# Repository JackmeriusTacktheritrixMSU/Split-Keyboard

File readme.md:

This is a split keyboard loosely based on Hack Club's (https://stasis.hackclub.com/starter-projects/split-keyboard.)
It runs from bluetooth, on two NRF52840 Pro Micro clone boards that you can get on aliexpress for cheap. 

Why'd I make it?
Its a bit of a deviation from the standard split keyboard dealy. Generally people use these same switches, but they

A. Expose the MCU on the top face of the keyboard halves
B. Use very few keys (Like a 45 percent keyboard or something along those lines)
and 
C. Use super flat, spread out keycaps.
I'm not crazy about any of these. I like traditional keyboards okay, and I have no idea how people remember which key is which on their splits. I wanted mine to be more standard- with the split for ergnomics but fairly status quo
everywhere else. I like the feeling of regular keycaps-- I like the look as well. I wanted to design my own keycaps. I got the little plug insert bits just from user fivedee on printables \
(https://www.printables.com/model/1069263-15x15-minimal-spaced-kailh-choc-keycap/files)  
Everything else I cut out and built my own. The result is some monster sized caps- turning low profile switches into a very much not low profile keyboard- which is what I wanted, but I might need to change things in the future and 
make my caps lighter. As of now they are untested. 

The design is screws coming up from the bottom. The two sides mesh together with a nice offset surface.

The PCB is actually reversed for the final- because it has kailh hot swap switches on it

BOM
| Item | Count | Price Per Unit | Total Price | Link | Status |
|---|---:|---:|---:|---|---|
| M2 Heatset Inserts (3.2 x 3.2mm) | 21 | N/A | N/A | N/A | Have |
| NRF52840 Dev Board | Pack x2 | N/A | $0.99 | [Link](https://www.aliexpress.us/item/3256807018711621.html?spm=a2g0o.cart.0.0.46a538daSh2DJS&mp=1&pdp_npi=6%40dis%21USD%21USD%207.23%21USD%200.99%21%21USD%200.99%21%21%21%402101e83017737027362077455e2f9f%2112000052145987931%21ct%21US%217434485779%21%211%210%21&_gl=1*qex46*_gcl_aw*R0NMLjE3NzM3MDE3OTIuQ2p3S0NBancxTjdOQmhBb0Vpd0FjUGNocDZjZm9MbWJFeHJpeEhseGhxQm5sM19CVXFTZWdTNlA5QUllUGg1SnFUQW82TlVySkJXMzF4b0N3UUVRQXZEX0J3RQ..*_gcl_dc*R0NMLjE3NzM3MDE3OTIuQ2p3S0NBancxTjdOQmhBb0Vpd0FjUGNocDZjZm9MbWJFeHJpeEhseGhxQm5sM19CVXFTZWdTNlA5QUllUGg1SnFUQW82TlVySkJXMzF4b0N3UUVRQXZEX0J3RQ..*_gcl_au*NDE0NzgwMTk1LjE3NzMxNzg3NzI.*_ga*MjEzOTYzMzUyMTA0MjEwOC4xNzczMTc4NzcxNDEx*_ga_VED1YSGNC7*czE3NzM3MDA1MzQkbzUkZzEkdDE3NzM3MDI3MzkkajMxJGwwJGgw&gatewayAdapt=glo2usa) | Need |
| PCB | Pack x5 (dev min) | N/A | $25.70 | N/A? | Need |
| Li-ion Poly Battery 5000mAh | Pack x2 | N/A | $14.13 | [Link](https://www.aliexpress.us/item/3256809787664995.html?spm=a2g0o.cart.0.0.610438daQ8KPR9&mp=1&pdp_npi=6%40dis%21USD%21USD%2031.41%21USD%2014.13%21%21USD%2014.13%21%21%21%402101e83017737024323317715e2f9f%2112000050732619666%21ct%21US%217434485779%21%211%210%21&_gl=1*4rofoi*_gcl_aw*R0NMLjE3NzM3MDE3OTIuQ2p3S0NBancxTjdOQmhBb0Vpd0FjUGNocDZjZm9MbWJFeHJpeEhseGhxQm5sM19CVXFTZWdTNlA5QUllUGg1SnFUQW82TlVySkJXMzF4b0N3UUVRQXZEX0J3RQ..*_gcl_dc*R0NMLjE3NzM3MDE3OTIuQ2p3S0NBancxTjdOQmhBb0Vpd0FjUGNocDZjZm9MbWJFeHJpeEhseGhxQm5sM19CVXFTZWdTNlA5QUllUGg1SnFUQW82TlVySkJXMzF4b0N3UUVRQXZEX0J3RQ..*_gcl_au*NDE0NzgwMTk1LjE3NzMxNzg3NzI.*_ga*MjEzOTYzMzUyMTA0MjEwOC4xNzczMTc4NzcxNDEx*_ga_VED1YSGNC7*czE3NzM3MDA1MzQkbzUkZzEkdDE3NzM3MDI3NDUkajI1JGwwJGgw&gatewayAdapt=glo2usa) | Need |
| Choc V1 Switches | 77 | N/A | N/A | [Link](https://www.aliexpress.us/item/3256809185516557.html?src=google&pdp_npi=4%40dis%21USD%217.09%217.09%21%21%21%21%21%40%2112000048898680192%21ppc%21%21%21&src=google&albch=shopping&acnt=708-803-3821&isdl=y&slnk=&plac=&mtctp=&albbt=Google_7_shopping&aff_platform=google&aff_short_key=UneMJZVf&gclsrc=aw.ds&albagn=888888&ds_e_adid=&ds_e_matchtype=&ds_e_device=c&ds_e_network=x&ds_e_product_group_id=&ds_e_product_id=en3256809185516557&ds_e_product_merchant_id=5337023700&ds_e_product_country=US&ds_e_product_language=en&ds_e_product_channel=online&ds_e_product_store_id=&ds_url_v=2&albcp=19558607238&albag=&isSmbAutoCall=false&needSmbHouyi=false&gad_source=1&gad_campaignid=19566915268&gbraid=0AAAAAD6I-hHE-H-7J2P63qEfKvxg4aSxQ&gclid=CjwKCAjw1N7NBhAoEiwAcPchp6cfoLmbExrixHlxhqBnl3_BUqSegS6P9AIePh5JqTAo6NUrJBW31xoCwQEQAvD_BwE&gatewayAdapt=glo2usa) | Have |
| PG1350 Sockets | 77 | N/A | N/A | [Link](https://www.aliexpress.us/item/3256805079542148.html?src=google&pdp_npi=4%40dis%21USD%211.54%211.11%21%21%21%21%21%40%2112000032415288517%21ppc%21%21%21&src=google&albch=shopping&acnt=708-803-3821&isdl=y&slnk=&plac=&mtctp=&albbt=Google_7_shopping&aff_platform=google&aff_short_key=UneMJZVf&gclsrc=aw.ds&albagn=888888&ds_e_adid=&ds_e_matchtype=&ds_e_device=c&ds_e_network=x&ds_e_product_group_id=&ds_e_product_id=en3256805079542148&ds_e_product_merchant_id=109258156&ds_e_product_country=US&ds_e_product_language=en&ds_e_product_channel=online&ds_e_product_store_id=&ds_url_v=2&albcp=19558607238&albag=&isSmbAutoCall=false&needSmbHouyi=false&gad_source=1&gad_campaignid=19566915268&gbraid=0AAAAAD6I-hHE-H-7J2P63qEfKvxg4aSxQ&gclid=CjwKCAjw1N7NBhAoEiwAcPchp13K3jXwFwk-rPK55fXNXv5V-aJNthOR1-a6wdnraypLKRLxYWzpIRoCTwwQAvD_BwE&gatewayAdapt=glo2usa) | Have |
| 1N4184W Diodes | 100 | N/A | $4.77 | [Link](https://www.aliexpress.us/item/3256809772352005.html?spm=a2g0o.cart.0.0.46a538daSh2DJS&mp=1&pdp_npi=6%40dis%21USD%21USD%209.54%21USD%204.77%21%21USD%204.77%21%21%21%402101e83017737027362077455e2f9f%2112000050691298739%21ct%21US%217434485779%21%211%210%21&_gl=1*4o9f7y*_gcl_aw*R0NMLjE3NzM3MDE3OTIuQ2p3S0NBancxTjdOQmhBb0Vpd0FjUGNocDZjZm9MbWJFeHJpeEhseGhxQm5sM19CVXFTZWdTNlA5QUllUGg1SnFUQW82TlVySkJXMzF4b0N3UUVRQXZEX0J3RQ..*_gcl_dc*R0NMLjE3NzM3MDE3OTIuQ2p3S0NBancxTjdOQmhBb0Vpd0FjUGNocDZjZm9MbWJFeHJpeEhseGhxQm5sM19CVXFTZWdTNlA5QUllUGg1SnFUQW82TlVySkJXMzF4b0N3UUVRQXZEX0J3RQ..*_gcl_au*NDE0NzgwMTk1LjE3NzMxNzg3NzI.*_ga*MjEzOTYzMzUyMTA0MjEwOC4xNzczMTc4NzcxNDEx*_ga_VED1YSGNC7*czE3NzM3MDA1MzQkbzUkZzEkdDE3NzM3MDI3MzUkajM1JGwwJGgw&gatewayAdapt=glo2usa) | Need |
| 0805 820k Ohm SMD resistor | 100 | N/A | N/A | N/A | Have? |
| 0805 2M Ohm SMD resistor | 100 | N/A | N/A | N/A | Have? |
| M2 Screws (20mm x8 and 4mm x8)| 16 | N/A | N/A | N/A | Have? |
| 3DPrinted Shells+Plate| 3 | N/A | N/A | N/A | Have? |
| Shipping |  |  | $20.73 |  |  |
| Coupons |  |  | -$13.00 |  |  |
| **Total** |  |  | **$53.32** |  |  |

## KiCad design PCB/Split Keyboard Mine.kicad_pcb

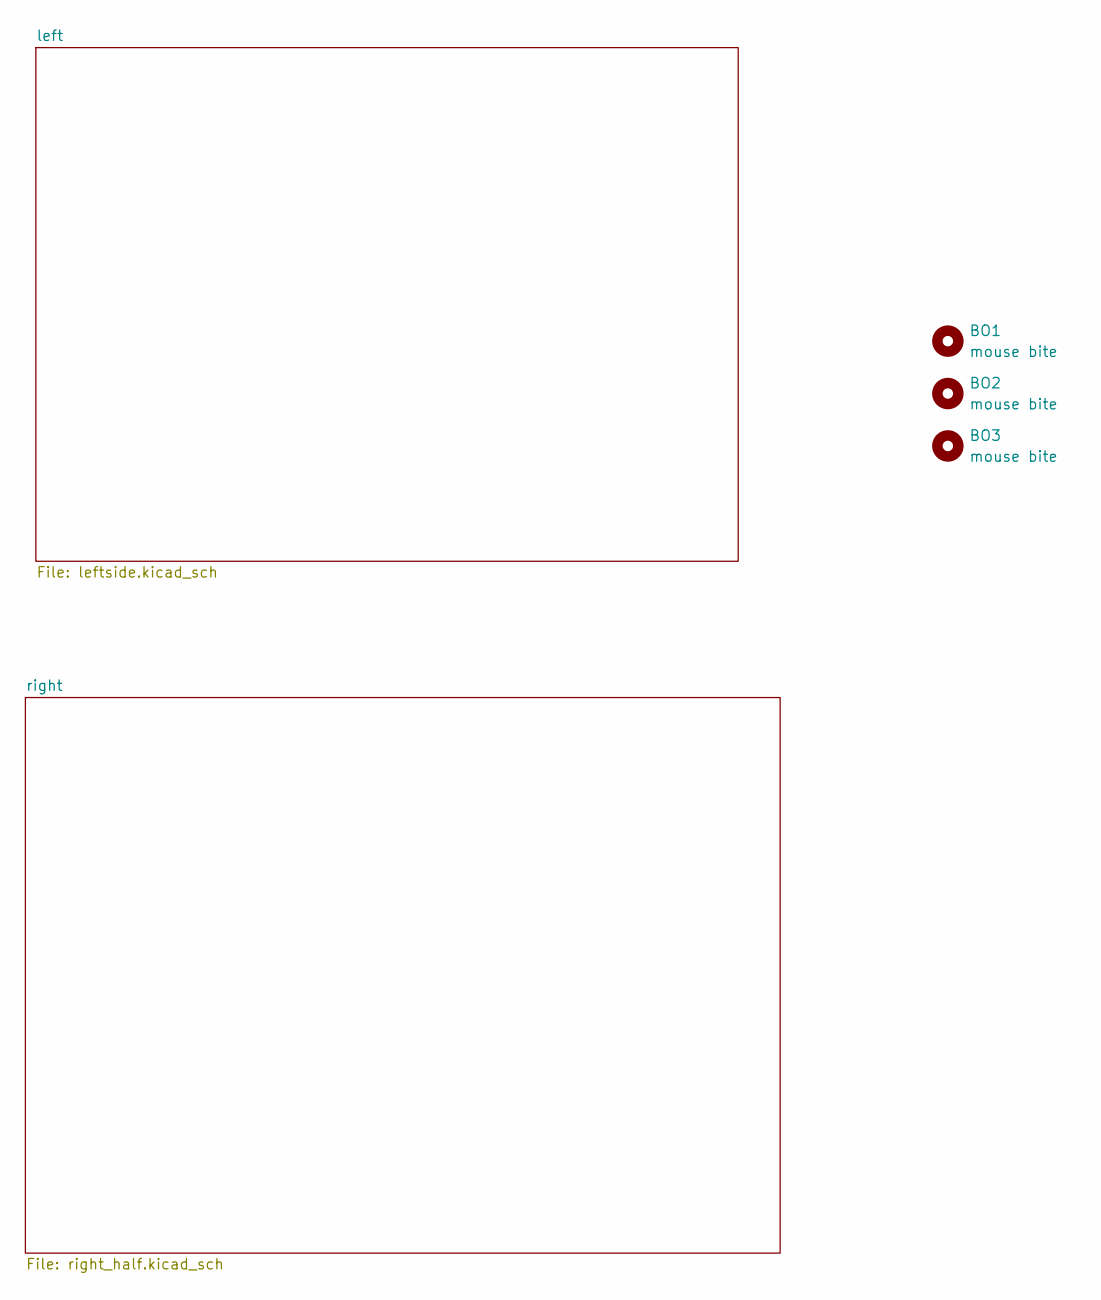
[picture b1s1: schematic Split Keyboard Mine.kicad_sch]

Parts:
BO1, BO2, BO3: mouse bite; mouse-bite-5mm-slot

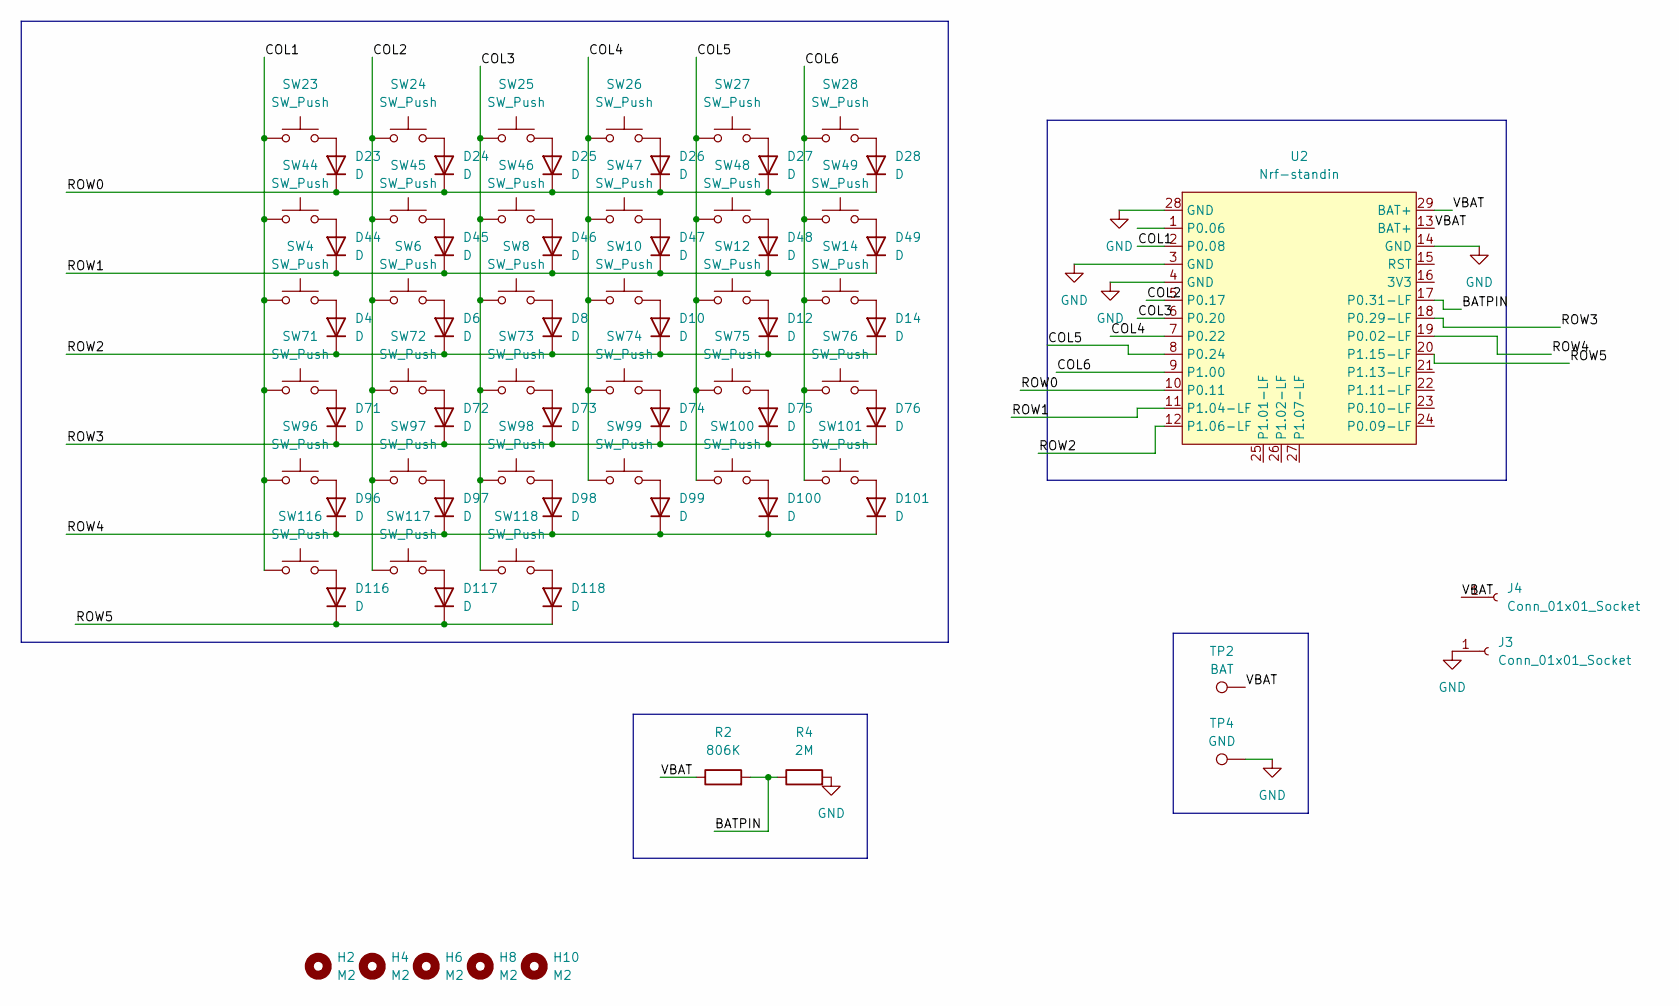
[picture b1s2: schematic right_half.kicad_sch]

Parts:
D4, D6, D8, D10, D12, D14, D23, D24, D25, D26, D27, D28, D44, D45, D46, D47, D48, D49, D71, D72, D73, D74, D75, D76, D96, D97, D98, D99, D100, D101, D116, D117, D118: D; D_SOD-123
H2, H4, H6, H8, H10: M2; MountingHole_2.2mm_M2
J3, J4: Conn_01x01_Socket; SolderWirePad_1x01_SMD_2x4mm
R2: 806K; R_0805_2012Metric
R4: 2M; R_0805_2012Metric
SW4, SW6, SW8, SW10, SW12, SW23, SW24, SW25, SW26, SW27, SW28, SW44, SW45, SW46, SW47, SW48, SW49, SW71, SW72, SW73, SW74, SW75, SW96, SW97, SW98, SW99, SW100, SW117, SW118: SW_Push; SW_choc_v1_HS_CPG135001S30_1u
SW14: SW_Push; SW_choc_v1_HS_CPG135001S30_1.25u
SW76: SW_Push; SW_choc_v1_HS_CPG135001S30_1.5u
SW101, SW116: SW_Push; SW_choc_v1_HS_CPG135001S30_1.75u
TP2: BAT; TestPoint_Pad_D2.0mm
TP4: GND; TestPoint_Pad_D2.0mm
U2: Nrf-standin; SuperMini_nRF52840_AH_Reversible

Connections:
/right/BATPIN: R2.2, R4.1, U2.17 (P0.31-LF)
/right/COL1: SW4.1, SW23.1, SW44.1, SW71.1, SW96.1, SW116.1, U2.2 (P0.08)
/right/COL2: SW6.1, SW24.1, SW45.1, SW72.1, SW97.1, SW117.1, U2.5 (P0.17)
/right/COL3: SW8.1, SW25.1, SW46.1, SW73.1, SW98.1, SW118.1, U2.6 (P0.20)
/right/COL4: SW10.1, SW26.1, SW47.1, SW74.1, SW99.1, U2.7 (P0.22)
/right/COL5: SW12.1, SW27.1, SW48.1, SW75.1, SW100.1, U2.8 (P0.24)
/right/COL6: SW14.1, SW28.1, SW49.1, SW76.1, SW101.1, U2.9 (P1.00)
/right/ROW0: D23.1 (K), D24.1 (K), D25.1 (K), D26.1 (K), D27.1 (K), D28.1 (K), U2.10 (P0.11)
/right/ROW1: D44.1 (K), D45.1 (K), D46.1 (K), D47.1 (K), D48.1 (K), D49.1 (K), U2.11 (P1.04-LF)
/right/ROW2: D4.1 (K), D6.1 (K), D8.1 (K), D10.1 (K), D12.1 (K), D14.1 (K), U2.12 (P1.06-LF)
/right/ROW3: D71.1 (K), D72.1 (K), D73.1 (K), D74.1 (K), D75.1 (K), D76.1 (K), U2.18 (P0.29-LF)
/right/ROW4: D96.1 (K), D97.1 (K), D98.1 (K), D99.1 (K), D100.1 (K), D101.1 (K), U2.19 (P0.02-LF)
/right/ROW5: D116.1 (K), D117.1 (K), D118.1 (K), U2.20 (P1.15-LF)
/right/VBAT: J4.1, R2.1, TP2.1, U2.13 (BAT+), U2.29 (BAT+)
GND: J3.1, R4.2, TP4.1, U2.3 (GND), U2.4 (GND), U2.14 (GND), U2.28 (GND); also elsewhere on the board
unnamed: D4.2 (A), SW4.2
unnamed: D6.2 (A), SW6.2
unnamed: D8.2 (A), SW8.2
unnamed: D10.2 (A), SW10.2
unnamed: D12.2 (A), SW12.2
unnamed: D14.2 (A), SW14.2
unnamed: D23.2 (A), SW23.2
unnamed: D24.2 (A), SW24.2
unnamed: D25.2 (A), SW25.2
unnamed: D26.2 (A), SW26.2
unnamed: D27.2 (A), SW27.2
unnamed: D28.2 (A), SW28.2
unnamed: D44.2 (A), SW44.2
unnamed: D45.2 (A), SW45.2
unnamed: D46.2 (A), SW46.2
unnamed: D47.2 (A), SW47.2
unnamed: D48.2 (A), SW48.2
unnamed: D49.2 (A), SW49.2
unnamed: D71.2 (A), SW71.2
unnamed: D72.2 (A), SW72.2
unnamed: D73.2 (A), SW73.2
unnamed: D74.2 (A), SW74.2
unnamed: D75.2 (A), SW75.2
unnamed: D76.2 (A), SW76.2
unnamed: D96.2 (A), SW96.2
unnamed: D97.2 (A), SW97.2
unnamed: D98.2 (A), SW98.2
unnamed: D99.2 (A), SW99.2
unnamed: D100.2 (A), SW100.2
unnamed: D101.2 (A), SW101.2
unnamed: D116.2 (A), SW116.2
unnamed: D117.2 (A), SW117.2
unnamed: D118.2 (A), SW118.2

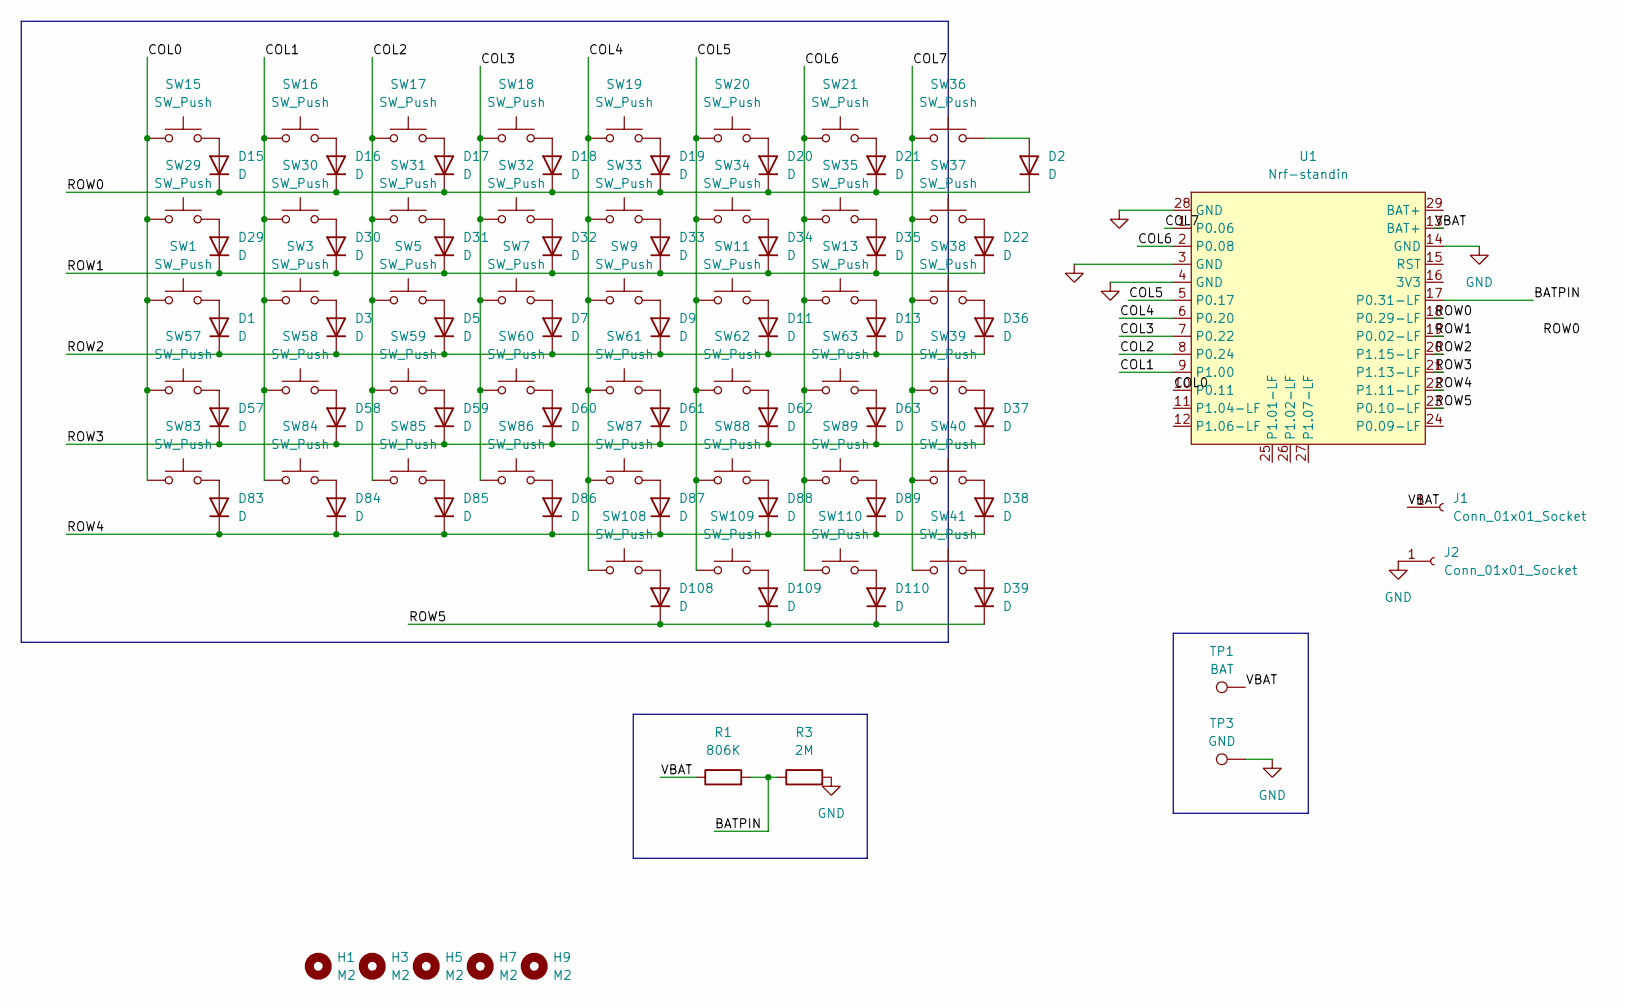
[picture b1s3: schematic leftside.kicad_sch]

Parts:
D1, D2, D3, D5, D7, D9, D11, D13, D15, D16, D17, D18, D19, D20, D21, D22, D29, D30, D31, D32, D33, D34, D35, D36, D37, D38, D39, D57, D58, D59, D60, D61, D62, D63, D83, D84, D85, D86, D87, D88, D89, D108, D109, D110: D; D_SOD-123
H1, H3, H5, H7, H9: M2; MountingHole_2.2mm_M2
J1, J2: Conn_01x01_Socket; SolderWirePad_1x01_SMD_2x4mm
R1: 806K; R_0805_2012Metric
R3: 2M; R_0805_2012Metric
SW1, SW57: SW_Push; SW_choc_v1_HS_CPG135001S30_1.25u
SW3, SW5, SW7, SW9, SW11, SW13, SW15, SW16, SW17, SW18, SW19, SW20, SW21, SW30, SW31, SW32, SW33, SW34, SW35, SW36, SW37, SW38, SW39, SW40, SW58, SW59, SW60, SW61, SW62, SW63, SW83, SW84, SW85, SW86, SW87, SW88, SW89, SW108, SW109, SW110: SW_Push; SW_choc_v1_HS_CPG135001S30_1u
SW29, SW41: SW_Push; SW_choc_v1_HS_CPG135001S30_1.75u
TP1: BAT; TestPoint_Pad_D2.0mm
TP3: GND; TestPoint_Pad_D2.0mm
U1: Nrf-standin; SuperMini_nRF52840_AH_Reversible

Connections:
/left/BATPIN: R1.2, R3.1, U1.17 (P0.31-LF)
/left/COL0: SW1.1, SW15.1, SW29.1, SW57.1, SW83.1, U1.10 (P0.11)
/left/COL1: SW3.1, SW16.1, SW30.1, SW58.1, SW84.1, U1.9 (P1.00)
/left/COL2: SW5.1, SW17.1, SW31.1, SW59.1, SW85.1, U1.8 (P0.24)
/left/COL3: SW7.1, SW18.1, SW32.1, SW60.1, SW86.1, U1.7 (P0.22)
/left/COL4: SW9.1, SW19.1, SW33.1, SW61.1, SW87.1, SW108.1, U1.6 (P0.20)
/left/COL5: SW11.1, SW20.1, SW34.1, SW62.1, SW88.1, SW109.1, U1.5 (P0.17)
/left/COL6: SW13.1, SW21.1, SW35.1, SW63.1, SW89.1, SW110.1, U1.2 (P0.08)
/left/COL7: SW36.1, SW37.1, SW38.1, SW39.1, SW40.1, SW41.1, U1.1 (P0.06)
/left/ROW0: D2.1 (K), D15.1 (K), D16.1 (K), D17.1 (K), D18.1 (K), D19.1 (K), D20.1 (K), D21.1 (K), U1.18 (P0.29-LF)
/left/ROW1: D22.1 (K), D29.1 (K), D30.1 (K), D31.1 (K), D32.1 (K), D33.1 (K), D34.1 (K), D35.1 (K), U1.19 (P0.02-LF)
/left/ROW2: D1.1 (K), D3.1 (K), D5.1 (K), D7.1 (K), D9.1 (K), D11.1 (K), D13.1 (K), D36.1 (K), U1.20 (P1.15-LF)
/left/ROW3: D37.1 (K), D57.1 (K), D58.1 (K), D59.1 (K), D60.1 (K), D61.1 (K), D62.1 (K), D63.1 (K), U1.21 (P1.13-LF)
/left/ROW4: D38.1 (K), D83.1 (K), D84.1 (K), D85.1 (K), D86.1 (K), D87.1 (K), D88.1 (K), D89.1 (K), U1.22 (P1.11-LF)
/left/ROW5: D39.1 (K), D108.1 (K), D109.1 (K), D110.1 (K), U1.23 (P0.10-LF)
/left/VBAT: J1.1, R1.1, TP1.1, U1.13 (BAT+)
GND: J2.1, R3.2, TP3.1, U1.3 (GND), U1.4 (GND), U1.14 (GND), U1.28 (GND); also elsewhere on the board
unnamed: D1.2 (A), SW1.2
unnamed: D2.2 (A), SW36.2
unnamed: D3.2 (A), SW3.2
unnamed: D5.2 (A), SW5.2
unnamed: D7.2 (A), SW7.2
unnamed: D9.2 (A), SW9.2
unnamed: D11.2 (A), SW11.2
unnamed: D13.2 (A), SW13.2
unnamed: D15.2 (A), SW15.2
unnamed: D16.2 (A), SW16.2
unnamed: D17.2 (A), SW17.2
unnamed: D18.2 (A), SW18.2
unnamed: D19.2 (A), SW19.2
unnamed: D20.2 (A), SW20.2
unnamed: D21.2 (A), SW21.2
unnamed: D22.2 (A), SW37.2
unnamed: D29.2 (A), SW29.2
unnamed: D30.2 (A), SW30.2
unnamed: D31.2 (A), SW31.2
unnamed: D32.2 (A), SW32.2
unnamed: D33.2 (A), SW33.2
unnamed: D34.2 (A), SW34.2
unnamed: D35.2 (A), SW35.2
unnamed: D36.2 (A), SW38.2
unnamed: D37.2 (A), SW39.2
unnamed: D38.2 (A), SW40.2
unnamed: D39.2 (A), SW41.2
unnamed: D57.2 (A), SW57.2
unnamed: D58.2 (A), SW58.2
unnamed: D59.2 (A), SW59.2
unnamed: D60.2 (A), SW60.2
unnamed: D61.2 (A), SW61.2
unnamed: D62.2 (A), SW62.2
unnamed: D63.2 (A), SW63.2
unnamed: D83.2 (A), SW83.2
unnamed: D84.2 (A), SW84.2
unnamed: D85.2 (A), SW85.2
unnamed: D86.2 (A), SW86.2
unnamed: D87.2 (A), SW87.2
unnamed: D88.2 (A), SW88.2
unnamed: D89.2 (A), SW89.2
unnamed: D108.2 (A), SW108.2
unnamed: D109.2 (A), SW109.2
unnamed: D110.2 (A), SW110.2

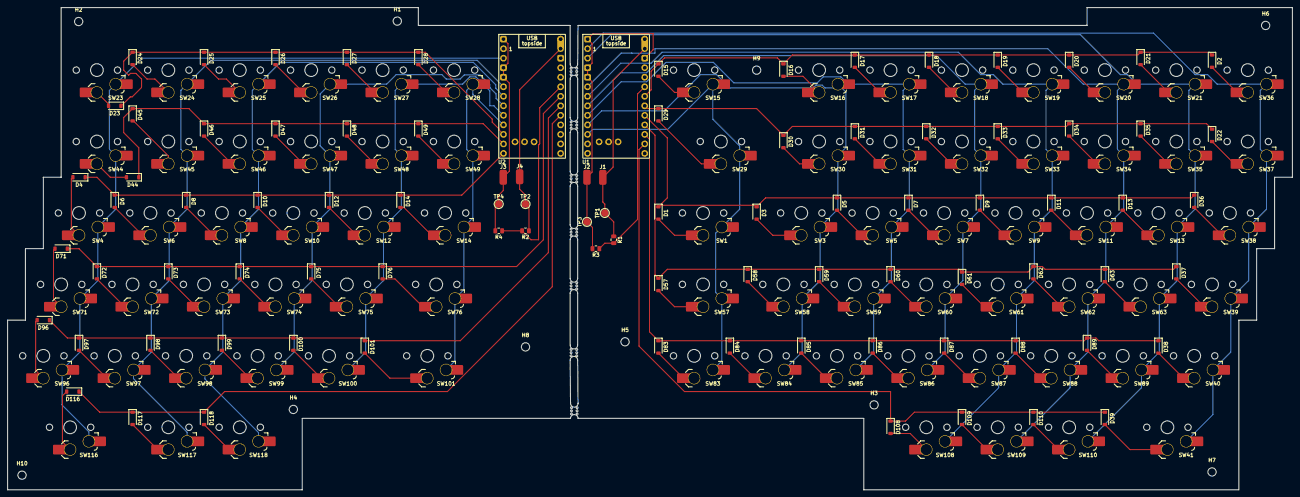
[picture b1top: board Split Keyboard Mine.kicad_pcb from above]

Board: 2 copper layers, 342.6 x 128.5 mm, 178 parts (0 on the bottom side), 108 nets.

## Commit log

2026-03-17 Finalizing
2026-03-17 Rename readme.txt.txt to readme.txt
